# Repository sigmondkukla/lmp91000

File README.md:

# EFR32BG24 Potentiostat Firmware & Debugger

This repository contains the C++ firmware for the custom potentiostat platform (featuring an LMP91000 analog front end, EFR32BG24 MCU, and an LSM6DSV IMU) alongside a Python-based real-time wireless BLE debugging client.

---

## 1. Prerequisites and Requirements

### Hardware

* Custom Potentiostat PCB (EFR32BG24, LMP91000, LSM6DSV)
* Segger J-Link or Simplicity Link Debugger
* A stable external power source (e.g., 3.3V bench power or a well-charged battery with adequate bulk capacitance)

### Software

* Simplicity Commander (added to your system PATH)
* Python 3.8 or newer
* Bleak Python library (for BLE communications)

---

## 2. Initial Setup (Wired Flashing)

Before the board can accept wireless updates, you must flash the bootloader and the initial application image via a physical JTAG/SWD debug connection.

### Step 1: Flash the Gecko Bootloader

The Gecko Bootloader is responsible for managing internal storage and installing GBL files. You must flash the combined bootloader image containing both the first-stage and main bootloader configurations.

```bash
commander flash bootloader-storage-internal-single-combined.s37 --device EFR32BG24

```

### Step 2: Flash the Application Firmware

Flash the initial C++ application binary:

```bash
commander flash potentiostat_app.s37 --device EFR32BG24

```

---

## 3. Over-The-Air (OTA) Firmware Updates

The custom board supports wireless updates using the Silicon Labs Apploader. When the board reboots into OTA mode, it will advertise as `OTA_potentiostat`.

### OTA Update Steps
#### *Make sure to hold down the power button during the entire OTA upload process, and for about 15-20 seconds after it finishes*

1. Build the firmware project to generate your target `.gbl` file.
2. Put the device into OTA mode. The device will stop regular advertising and begin advertising as `OTA_potentiostat`.
3. Open the **EFR Connect** app on your smartphone or pc.
4. Scan and connect to **OTA_potentiostat**.
5. Select **OTA DFU**, choose **Partial OTA** (or select your `.gbl` file), and initiate the transfer.
6. Upon reaching 100%, the chip will reboot, verify the image, and boot into your new application.

---

## 4. Real-Time Wireless Log Stream

The firmware includes a high-speed wireless logger that routes standard debug prints over a custom BLE characteristic.

### Installation

Install the required asynchronous BLE library:

```bash
pip install bleak

```

### Python Logger Client: `ble_logger.py`

### Usage

1. Power on your potentiostat board.
2. Run the client script:
```bash
python ble_logger.py

```

3. The script will automatically scan, establish a secure BLE connection to your EFR32, subscribe to the notifications, and print custom `ble_printf` debug logs directly to your console.

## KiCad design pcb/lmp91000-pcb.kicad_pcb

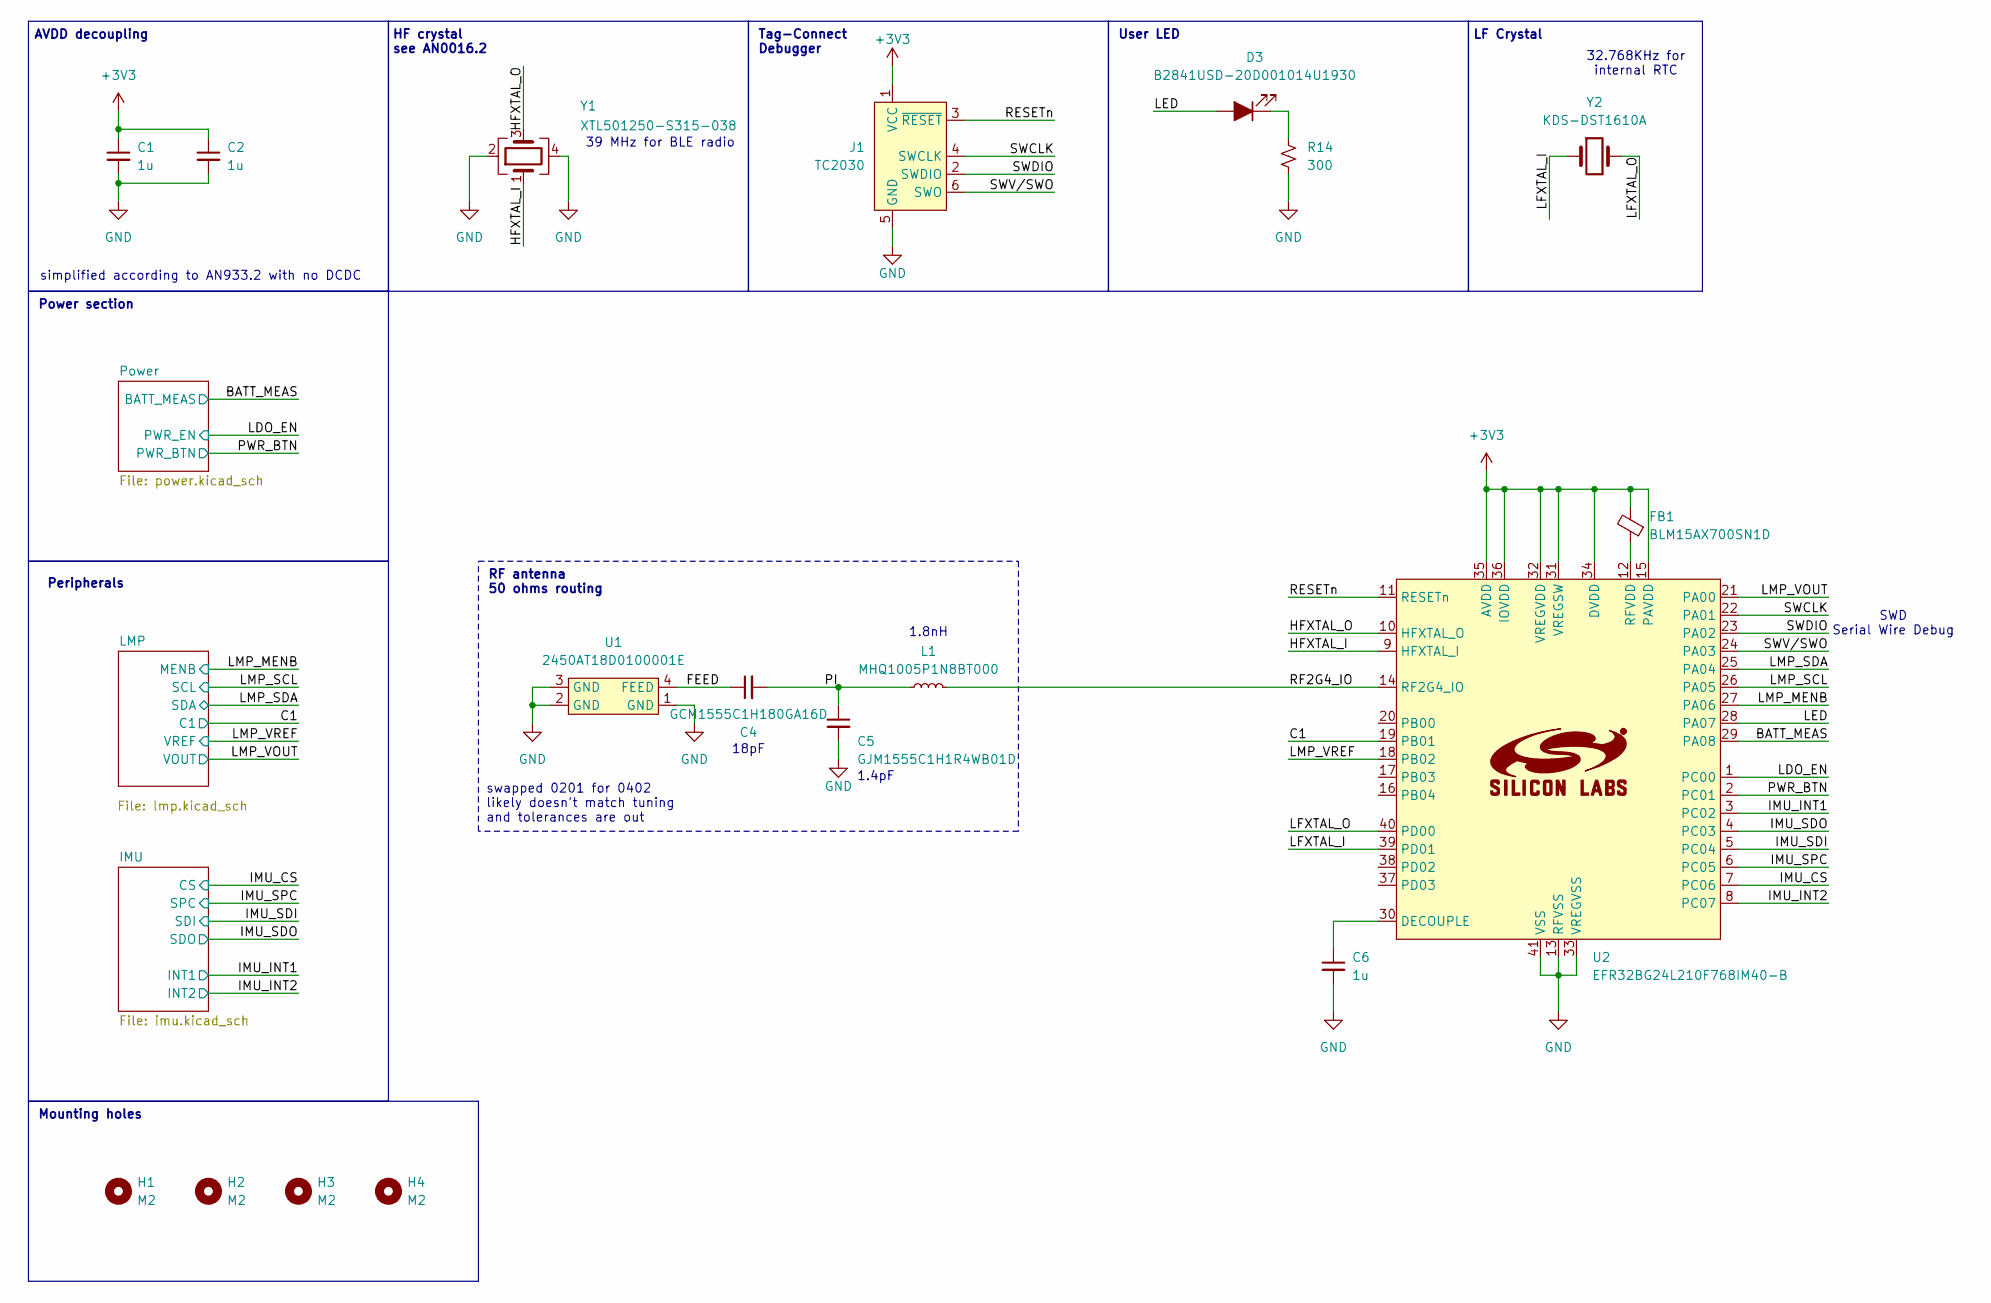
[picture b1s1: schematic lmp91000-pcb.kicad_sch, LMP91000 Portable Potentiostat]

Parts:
C1, C2, C6: 1u; C_0402_1005Metric
C4: GCM1555C1H180GA16D; C_0402_1005Metric
C5: GJM1555C1H1R4WB01D; C_0402_1005Metric
D3: B2841USD-20D001014U1930; LED_0402_1005Metric
FB1: BLM15AX700SN1D; L_0402_1005Metric
H1, H2, H3, H4: M2; MountingHole_2.2mm_M2
J1: TC2030; Tag-Connect_TC2030-IDC-NL_2x03_P1.27mm_Vertical
L1: MHQ1005P1N8BT000; L_0402_1005Metric
R14: 300; R_0402_1005Metric
U1: 2450AT18D0100001E; Johanson_2450AT18D0100001E
U2: EFR32BG24L210F768IM40-B; QFN-40-1EP_5x5mm_P0.4mm_EP3.8x3.8mm
Y1: XTL501250-S315-038; Crystal_SMD_2016-4Pin_2.0x1.6mm
Y2: KDS-DST1610A

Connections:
+3V3: C1.1, C2.1, FB1.2, J1.1 (VCC), U2.15 (PAVDD), U2.31 (VREGSW), U2.32 (VREGVDD), U2.34 (DVDD), U2.35 (AVDD), U2.36 (IOVDD); also elsewhere on the board
/BATT_MEAS: U2.29 (PA08); also elsewhere on the board
/C1: U2.19 (PB01); also elsewhere on the board
/FEED: C4.1, U1.4 (FEED)
/HFXTAL_I: U2.9 (HFXTAL_I), Y1.1
/HFXTAL_O: U2.10 (HFXTAL_O), Y1.3
/IMU_CS: U2.7 (PC06); also elsewhere on the board
/IMU_INT1: U2.3 (PC02); also elsewhere on the board
/IMU_INT2: U2.8 (PC07); also elsewhere on the board
/IMU_SDI: U2.5 (PC04); also elsewhere on the board
/IMU_SDO: U2.4 (PC03); also elsewhere on the board
/IMU_SPC: U2.6 (PC05); also elsewhere on the board
/LDO_EN: U2.1 (PC00); also elsewhere on the board
/LED: D3.2 (A), U2.28 (PA07)
/LFXTAL_I: U2.39 (PD01), Y2.1
/LFXTAL_O: U2.40 (PD00), Y2.2
/LMP_MENB: U2.27 (PA06); also elsewhere on the board
/LMP_SCL: U2.26 (PA05); also elsewhere on the board
/LMP_SDA: U2.25 (PA04); also elsewhere on the board
/LMP_VOUT: U2.21 (PA00); also elsewhere on the board
/LMP_VREF: U2.18 (PB02); also elsewhere on the board
/PI: C4.2, C5.1, L1.1
/PWR_BTN: U2.2 (PC01); also elsewhere on the board
/RESETn: J1.3 (~RESET), U2.11 (RESETn)
/RF2G4_IO: L1.2, U2.14 (RF2G4_IO)
/SWCLK: J1.4 (SWCLK), U2.22 (PA01)
/SWDIO: J1.2 (SWDIO), U2.23 (PA02)
/SWV/SWO: J1.6 (SWO), U2.24 (PA03)
GND: C1.2, C2.2, C5.2, C6.2, J1.5 (GND), R14.2, U1.1 (GND), U1.2 (GND), U1.3 (GND), U2.13 (RFVSS), U2.33 (VREGVSS), U2.41 (VSS), Y1.2, Y1.4; also elsewhere on the board
unnamed: D3.1 (K), R14.1
unnamed: C6.1, U2.30 (DECOUPLE)
unnamed: FB1.1, U2.12 (RFVDD)

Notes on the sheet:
1.4pF
User LED
Peripherals
1.8nH
32.768KHz for internal RTC
simplified according to AN933.2 with no DCDC
HF crystal see AN0016.2
SWD Serial Wire Debug
RF antenna 50 ohms routing
Tag-Connect Debugger
Mounting holes
39 MHz for BLE radio
LF Crystal
swapped 0201 for 0402 likely doesn't match tuning and tolerances are out
18pF
Power section
AVDD decoupling

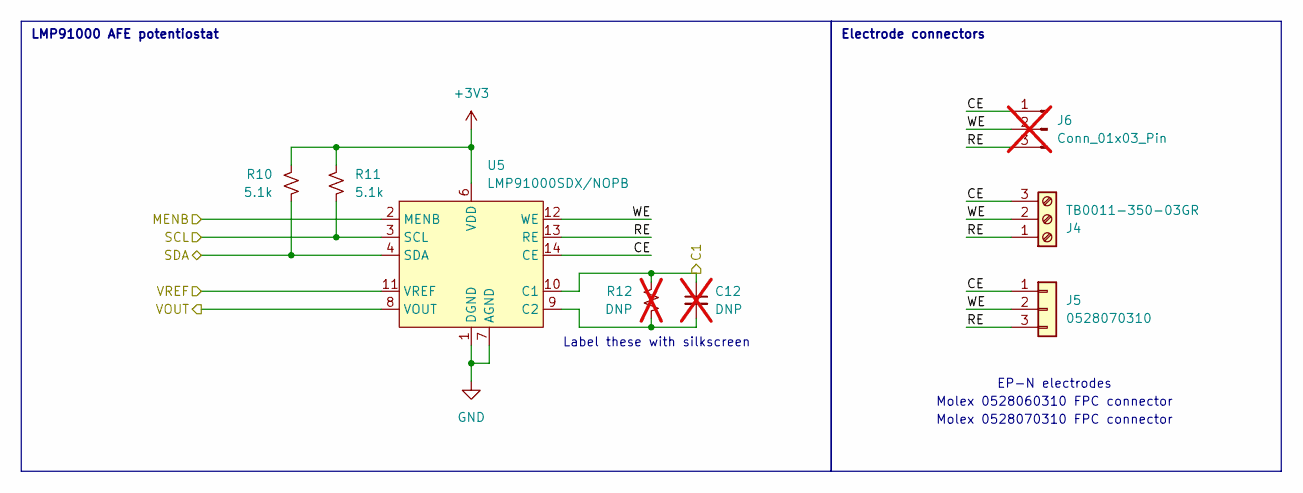
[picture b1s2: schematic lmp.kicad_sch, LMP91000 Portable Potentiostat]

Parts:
C12: DNP; C_0603_1608Metric_Pad1.08x0.95mm_HandSolder; not fitted
J4: TB0011-350-03GR; SAMESKY_TB0011-350-03GR
J5: 0528070310; 528070310
J6: Conn_01x03_Pin; PinHeader_1x03_P2.54mm_Vertical; not fitted
R10, R11: 5.1k; R_0402_1005Metric
R12: DNP; R_0603_1608Metric_Pad0.98x0.95mm_HandSolder; not fitted
U5: LMP91000SDX/NOPB; WSON-14-1EP_4.0x4.0mm_P0.5mm_EP2.6x2.6mm

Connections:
+3V3: R10.2, R11.2, U5.6 (VDD); also elsewhere on the board
/C1: C12.1, R12.1, U5.10 (C1); also elsewhere on the board
/LMP/CE: J4.3, J5.1, J6.1, U5.14 (CE)
/LMP/RE: J4.1, J5.3, J6.3, U5.13 (RE)
/LMP/WE: J4.2, J5.2, J6.2, U5.12 (WE)
/LMP_MENB: U5.2 (MENB); also elsewhere on the board
/LMP_SCL: R11.1, U5.3 (SCL); also elsewhere on the board
/LMP_SDA: R10.1, U5.4 (SDA); also elsewhere on the board
/LMP_VOUT: U5.8 (VOUT); also elsewhere on the board
/LMP_VREF: U5.11 (VREF); also elsewhere on the board
GND: U5.1 (DGND), U5.7 (AGND), U5.15 (DAP); also elsewhere on the board
unnamed: C12.2, R12.2, U5.9 (C2)

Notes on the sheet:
Label these with silkscreen
Molex 0528070310 FPC connector
EP-N electrodes
Molex 0528060310 FPC connector
LMP91000 AFE potentiostat
Electrode connectors

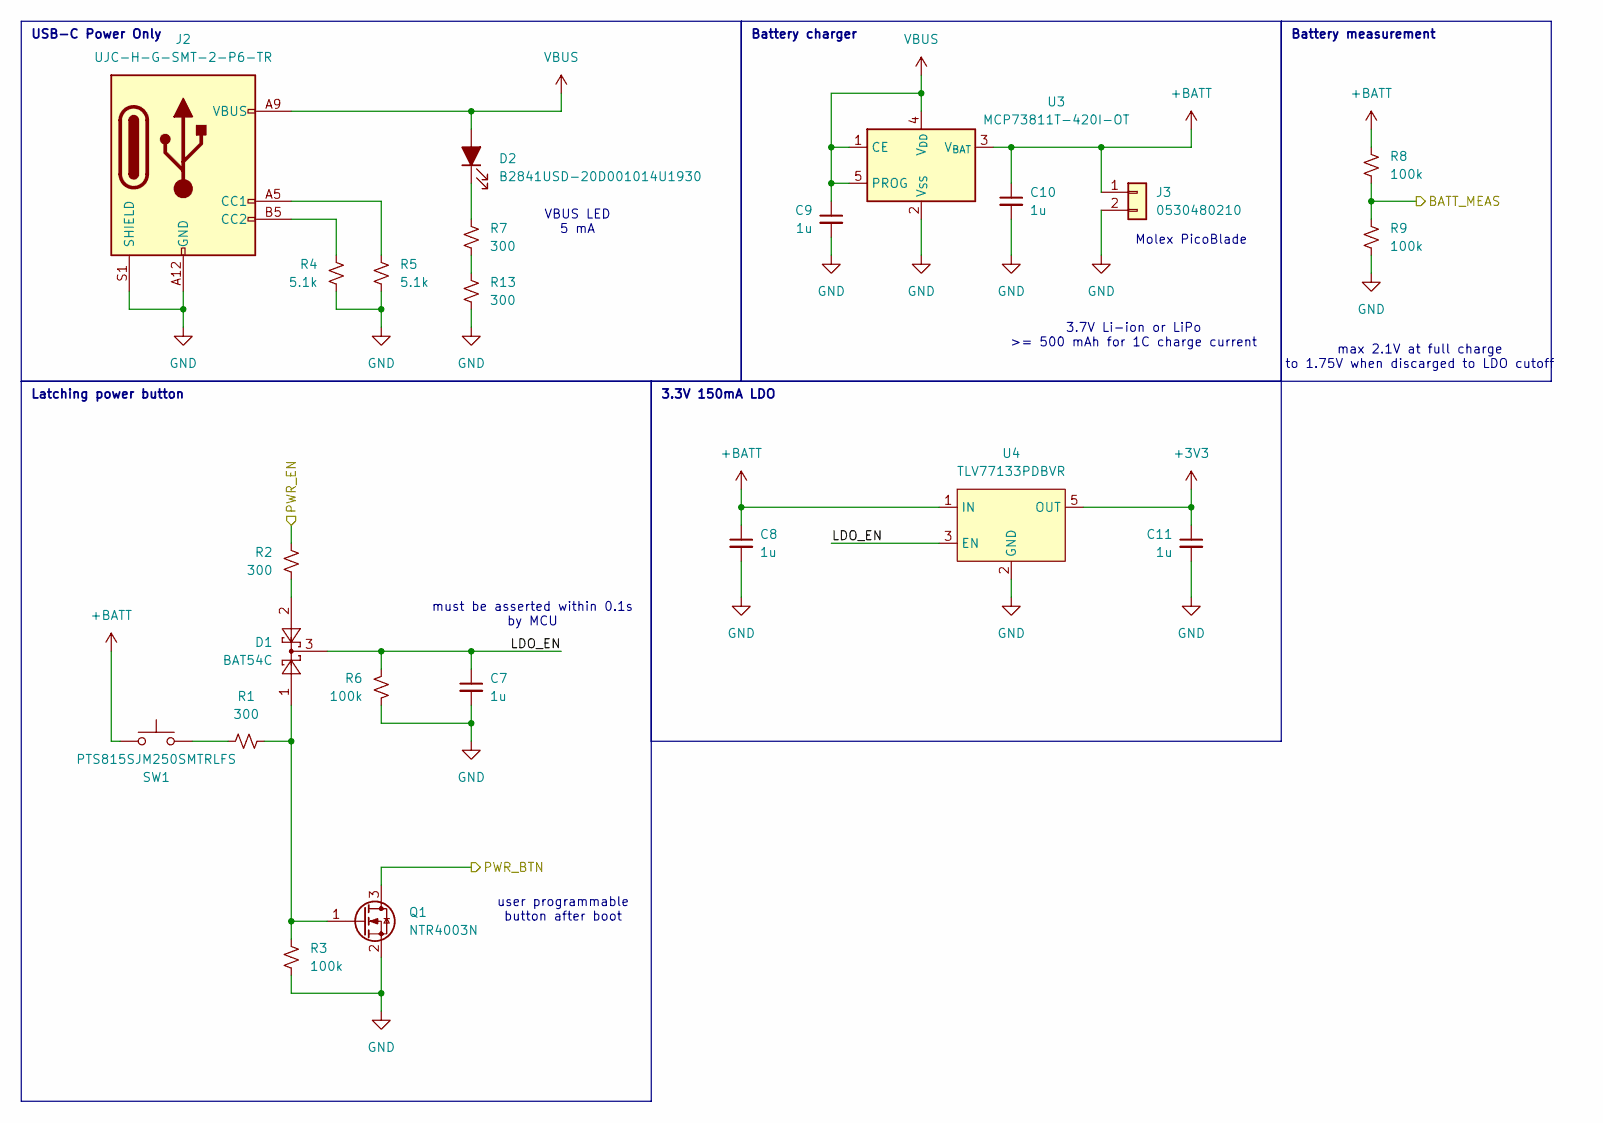
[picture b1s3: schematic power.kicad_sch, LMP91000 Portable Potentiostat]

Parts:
C7, C8, C9, C10, C11: 1u; C_0402_1005Metric
D1: BAT54C; SOT-23
D2: B2841USD-20D001014U1930; LED_0402_1005Metric
J2: UJC-H-G-SMT-2-P6-TR; SAMESKY_UJC-H-G-SMT-2-P6-TR
J3: 0530480210; Molex_PicoBlade_53048-0210_1x02_P1.25mm_Horizontal
Q1: NTR4003N; SOT-23
R1, R2, R7, R13: 300; R_0402_1005Metric
R3, R6, R8, R9: 100k; R_0402_1005Metric
R4, R5: 5.1k; R_0402_1005Metric
SW1: PTS815SJM250SMTRLFS; SW_Push_PTS815_SJM_250_SMTR_LFS
U3: MCP73811T-420I-OT; SOT-23-5
U4: TLV77133PDBVR; SOT-23-5

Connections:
+3V3: C11.1, U4.5 (OUT); also elsewhere on the board
+BATT: C8.1, C10.1, J3.1, R8.1, SW1.1, U3.3 (V_{BAT}), U4.1 (IN)
/BATT_MEAS: R8.2, R9.1; also elsewhere on the board
/LDO_EN: R2.1; also elsewhere on the board
/PWR_BTN: Q1.3 (D); also elsewhere on the board
/Power/LDO_EN: C7.1, D1.3, R6.1, U4.3 (EN)
GND: C7.2, C8.2, C9.2, C10.2, C11.2, J2.A12 (GND), J2.B12 (GND), J2.S1 (SHIELD), J3.2, Q1.2 (S), R3.2, R4.1, R5.1, R6.2, R9.2, R13.2, U3.2 (V_{SS}), U4.2 (GND), U4.4 (NC); also elsewhere on the board
unnamed: D1.2, R2.2
unnamed: D2.1 (K), R7.1
unnamed: J2.A5 (CC1), R5.2
unnamed: J2.B5 (CC2), R4.2
unnamed: D1.1, Q1.1 (G), R1.2, R3.1
unnamed: R1.1, SW1.2
unnamed: R7.2, R13.1
VBUS: C9.1, D2.2 (A), J2.A9 (VBUS), J2.B9 (VBUS), U3.1 (CE), U3.4 (V_{DD}), U3.5 (PROG)

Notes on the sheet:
USB-C Power Only
must be asserted within 0.1s by MCU
3.7V Li-ion or LiPo >= 500 mAh for 1C charge current
VBUS LED 5 mA
Molex PicoBlade
Battery charger
Battery measurement
Latching power button
3.3V 150mA LDO
user programmable button after boot
max 2.1V at full charge to 1.75V when discarged to LDO cutoff

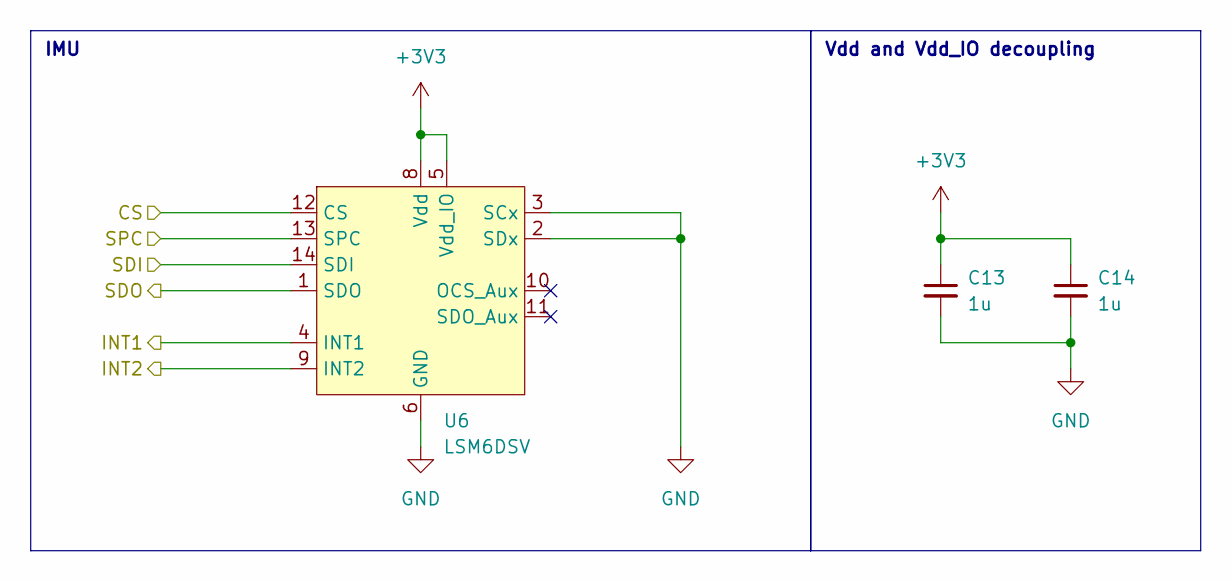
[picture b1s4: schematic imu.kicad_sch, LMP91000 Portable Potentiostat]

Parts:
C13, C14: 1u; C_0402_1005Metric
U6: LSM6DSV; LGA-14_3x2.5mm_P0.5mm_LayoutBorder3x4y

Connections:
+3V3: C13.1, C14.1, U6.5 (Vdd_IO), U6.8 (Vdd); also elsewhere on the board
/IMU_CS: U6.12 (CS); also elsewhere on the board
/IMU_INT1: U6.4 (INT1); also elsewhere on the board
/IMU_INT2: U6.9 (INT2); also elsewhere on the board
/IMU_SDI: U6.14 (SDI); also elsewhere on the board
/IMU_SDO: U6.1 (SDO); also elsewhere on the board
/IMU_SPC: U6.13 (SPC); also elsewhere on the board
GND: C13.2, C14.2, U6.2 (SDx), U6.3 (SCx), U6.6 (GND), U6.7 (GND); also elsewhere on the board

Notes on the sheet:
IMU
Vdd and Vdd_IO decoupling

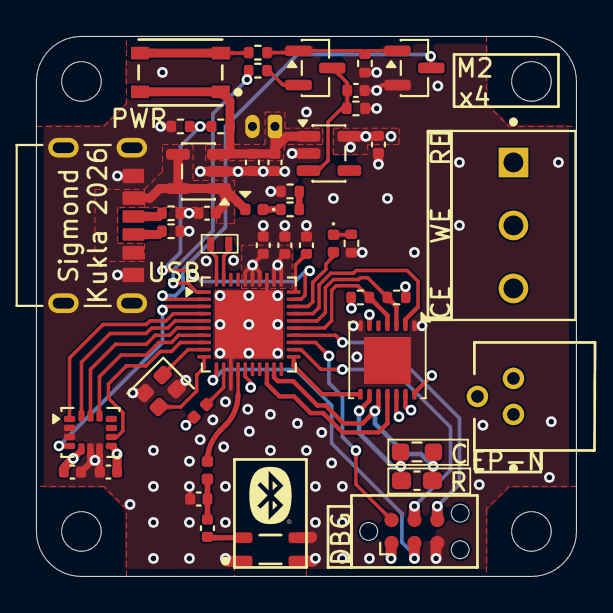
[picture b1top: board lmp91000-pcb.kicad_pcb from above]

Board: 4 copper layers, 30.0 x 30.0 mm, 51 parts (1 on the bottom side), 46 nets.

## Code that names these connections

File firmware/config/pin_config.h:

#ifndef PIN_CONFIG_H
#define PIN_CONFIG_H

// $[CMU]
// [CMU]$

// $[LFXO]
// [LFXO]$

// $[PRS.ASYNCH0]
// [PRS.ASYNCH0]$

// $[PRS.ASYNCH1]
// [PRS.ASYNCH1]$

// $[PRS.ASYNCH2]
// [PRS.ASYNCH2]$

// $[PRS.ASYNCH3]
// [PRS.ASYNCH3]$

// $[PRS.ASYNCH4]
// [PRS.ASYNCH4]$

// $[PRS.ASYNCH5]
// [PRS.ASYNCH5]$

// $[PRS.ASYNCH6]
// [PRS.ASYNCH6]$

// $[PRS.ASYNCH7]
// [PRS.ASYNCH7]$

// $[PRS.ASYNCH8]
// [PRS.ASYNCH8]$

// $[PRS.ASYNCH9]
// [PRS.ASYNCH9]$

// $[PRS.ASYNCH10]
// [PRS.ASYNCH10]$

// $[PRS.ASYNCH11]
// [PRS.ASYNCH11]$

// $[PRS.ASYNCH12]
// [PRS.ASYNCH12]$

// $[PRS.ASYNCH13]
// [PRS.ASYNCH13]$

// $[PRS.ASYNCH14]
// [PRS.ASYNCH14]$

// $[PRS.ASYNCH15]
// [PRS.ASYNCH15]$

// $[PRS.SYNCH0]
// [PRS.SYNCH0]$

// $[PRS.SYNCH1]
// [PRS.SYNCH1]$

// $[PRS.SYNCH2]
// [PRS.SYNCH2]$

// $[PRS.SYNCH3]
// [PRS.SYNCH3]$

// $[GPIO]
// GPIO SWCLK on PA01
#ifndef GPIO_SWCLK_PORT                         
#define GPIO_SWCLK_PORT                          SL_GPIO_PORT_A
#endif
#ifndef GPIO_SWCLK_PIN                          
#define GPIO_SWCLK_PIN                           1
#endif

// GPIO SWDIO on PA02
#ifndef GPIO_SWDIO_PORT                         
#define GPIO_SWDIO_PORT                          SL_GPIO_PORT_A
#endif
#ifndef GPIO_SWDIO_PIN                          
#define GPIO_SWDIO_PIN                           2
#endif

// GPIO SWV on PA03
#ifndef GPIO_SWV_PORT                           
#define GPIO_SWV_PORT                            SL_GPIO_PORT_A
#endif
#ifndef GPIO_SWV_PIN                            
#define GPIO_SWV_PIN                             3
#endif

// [GPIO]$

// $[TIMER0]
// [TIMER0]$

// $[TIMER1]
// [TIMER1]$

// $[TIMER2]
// [TIMER2]$

// $[TIMER3]
// [TIMER3]$

// $[TIMER4]
// [TIMER4]$

// $[USART0]
// [USART0]$

// $[I2C1]
// [I2C1]$

// $[EUSART1]
// [EUSART1]$

// $[KEYSCAN]
// [KEYSCAN]$

// $[LETIMER0]
// [LETIMER0]$

// $[IADC0]
// IADC0 POS on PA00
#ifndef IADC0_POS_PORT                          
#define IADC0_POS_PORT                           SL_GPIO_PORT_A
#endif
#ifndef IADC0_POS_PIN                           
#define IADC0_POS_PIN                            0
#endif

// [IADC0]$

// $[ACMP0]
// [ACMP0]$

// $[ACMP1]
// [ACMP1]$

// $[VDAC0]
// VDAC0 CH0_MAIN_OUT on PB00
#ifndef VDAC0_CH0_MAIN_OUT_PORT                 
#define VDAC0_CH0_MAIN_OUT_PORT                  SL_GPIO_PORT_B
#endif
#ifndef VDAC0_CH0_MAIN_OUT_PIN                  
#define VDAC0_CH0_MAIN_OUT_PIN                   0
#endif

// [VDAC0]$

// $[VDAC1]
// [VDAC1]$

// $[PCNT0]
// [PCNT0]$

// $[HFXO0]
// [HFXO0]$

// $[I2C0]
// I2C0 SCL on PA05
#ifndef I2C0_SCL_PORT                           
#define I2C0_SCL_PORT                            SL_GPIO_PORT_A
#endif
#ifndef I2C0_SCL_PIN                            
#define I2C0_SCL_PIN                             5
#endif

// I2C0 SDA on PA04
#ifndef I2C0_SDA_PORT                           
#define I2C0_SDA_PORT                            SL_GPIO_PORT_A
#endif
#ifndef I2C0_SDA_PIN                            
#define I2C0_SDA_PIN                             4
#endif

// [I2C0]$

// $[EUSART0]
// [EUSART0]$

// $[PTI]
// [PTI]$

// $[MODEM]
// [MODEM]$

// $[CUSTOM_PIN_NAME]
#ifndef LMP_VOUT_PORT                           
#define LMP_VOUT_PORT                            SL_GPIO_PORT_A
#endif
#ifndef LMP_VOUT_PIN                            
#define LMP_VOUT_PIN                             0
#endif

#ifndef LMP_SDA_PORT                            
#define LMP_SDA_PORT                             SL_GPIO_PORT_A
#endif
#ifndef LMP_SDA_PIN                             
#define LMP_SDA_PIN                              4
#endif

#ifndef LMP_SCL_PORT                            
#define LMP_SCL_PORT                             SL_GPIO_PORT_A
#endif
#ifndef LMP_SCL_PIN                             
#define LMP_SCL_PIN                              5
#endif

#ifndef LED_PORT                                
#define LED_PORT                                 SL_GPIO_PORT_A
#endif
#ifndef LED_PIN                                 
#define LED_PIN                                  8
#endif

#ifndef LMP_VREF_PORT                           
#define LMP_VREF_PORT                            SL_GPIO_PORT_B
#endif
#ifndef LMP_VREF_PIN                            
#define LMP_VREF_PIN                             0
#endif

#ifndef LDO_EN_PORT                             
#define LDO_EN_PORT                              SL_GPIO_PORT_C
#endif
#ifndef LDO_EN_PIN                              
#define LDO_EN_PIN                               0
#endif

#ifndef PWR_BTN_PORT                            
#define PWR_BTN_PORT                             SL_GPIO_PORT_C
#endif
#ifndef PWR_BTN_PIN                             
#define PWR_BTN_PIN                              1
#endif

#ifndef IMU_SDO_PORT                            
#define IMU_SDO_PORT                             SL_GPIO_PORT_C
#endif
#ifndef IMU_SDO_PIN                             
#define IMU_SDO_PIN                              3
#endif

#ifndef IMU_SDI_PORT                            
#define IMU_SDI_PORT                             SL_GPIO_PORT_C
#endif
#ifndef IMU_SDI_PIN                             
#define IMU_SDI_PIN                              4
#endif

#ifndef IMU_SPC_PORT                            
#define IMU_SPC_PORT                             SL_GPIO_PORT_C
#endif
#ifndef IMU_SPC_PIN                             
#define IMU_SPC_PIN                              5
#endif

#ifndef IMU_CS_PORT                             
#define IMU_CS_PORT                              SL_GPIO_PORT_C
#endif
#ifndef IMU_CS_PIN                              
#define IMU_CS_PIN                               6
#endif

#ifndef IMU_INT2_PORT                           
#define IMU_INT2_PORT                            SL_GPIO_PORT_C
#endif
#ifndef IMU_INT2_PIN                            
#define IMU_INT2_PIN                             7
#endif

#ifndef BATT_MEAS_PORT                          
#define BATT_MEAS_PORT                           SL_GPIO_PORT_D
#endif
#ifndef BATT_MEAS_PIN                           
#define BATT_MEAS_PIN                            0
#endif

// [CUSTOM_PIN_NAME]$


#endif // PIN_CONFIG_H

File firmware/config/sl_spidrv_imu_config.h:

/***************************************************************************//**
 * @file
 * @brief SPIDRV Config
 *******************************************************************************
 * # License
 * <b>Copyright 2019 Silicon Laboratories Inc. www.silabs.com</b>
 *******************************************************************************
 *
 * SPDX-License-Identifier: Zlib
 *
 * The licensor of this software is Silicon Laboratories Inc.
 *
 * This software is provided 'as-is', without any express or implied
 * warranty. In no event will the authors be held liable for any damages
 * arising from the use of this software.
 *
 * Permission is granted to anyone to use this software for any purpose,
 * including commercial applications, and to alter it and redistribute it
 * freely, subject to the following restrictions:
 *
 * 1. The origin of this software must not be misrepresented; you must not
 *    claim that you wrote the original software. If you use this software
 *    in a product, an acknowledgment in the product documentation would be
 *    appreciated but is not required.
 * 2. Altered source versions must be plainly marked as such, and must not be
 *    misrepresented as being the original software.
 * 3. This notice may not be removed or altered from any source distribution.
 *
 ******************************************************************************/

#ifndef SL_SPIDRV_IMU_CONFIG_H
#define SL_SPIDRV_IMU_CONFIG_H

#include "spidrv.h"

// <<< Use Configuration Wizard in Context Menu >>>
// <h> SPIDRV settings

// <o SL_SPIDRV_IMU_BITRATE> SPI bitrate
// <i> Default: 1000000
#define SL_SPIDRV_IMU_BITRATE           1000000

// <o SL_SPIDRV_IMU_FRAME_LENGTH> SPI frame length <4-16>
// <i> Default: 8
#define SL_SPIDRV_IMU_FRAME_LENGTH      8

// <o SL_SPIDRV_IMU_TYPE> SPI mode
// <spidrvMaster=> Master
// <spidrvSlave=> Slave
#define SL_SPIDRV_IMU_TYPE              spidrvMaster

// <o SL_SPIDRV_IMU_BIT_ORDER> Bit order on the SPI bus
// <spidrvBitOrderLsbFirst=> LSB transmitted first
// <spidrvBitOrderMsbFirst=> MSB transmitted first
#define SL_SPIDRV_IMU_BIT_ORDER         spidrvBitOrderMsbFirst

// <o SL_SPIDRV_IMU_CLOCK_MODE> SPI clock mode
// <spidrvClockMode0=> SPI mode 0: CLKPOL=0, CLKPHA=0
// <spidrvClockMode1=> SPI mode 1: CLKPOL=0, CLKPHA=1
// <spidrvClockMode2=> SPI mode 2: CLKPOL=1, CLKPHA=0
// <spidrvClockMode3=> SPI mode 3: CLKPOL=1, CLKPHA=1
#define SL_SPIDRV_IMU_CLOCK_MODE        spidrvClockMode0

// <o SL_SPIDRV_IMU_CS_CONTROL> SPI master chip select (CS) control scheme.
// <spidrvCsControlAuto=> CS controlled by the SPI driver
// <spidrvCsControlApplication=> CS controlled by the application
#define SL_SPIDRV_IMU_CS_CONTROL        spidrvCsControlAuto

// <o SL_SPIDRV_IMU_SLAVE_START_MODE> SPI slave transfer start scheme
// <spidrvSlaveStartImmediate=> Transfer starts immediately
// <spidrvSlaveStartDelayed=> Transfer starts when the bus is idle (CS deasserted)
// <i> Only applies if instance type is spidrvSlave
#define SL_SPIDRV_IMU_SLAVE_START_MODE  spidrvSlaveStartImmediate
// </h>
// <<< end of configuration section >>>

// <<< sl:start pin_tool >>>
// <usart signal=TX,RX,CLK,(CS)> SL_SPIDRV_IMU
// $[USART_SL_SPIDRV_IMU]
#ifndef SL_SPIDRV_IMU_PERIPHERAL                
#define SL_SPIDRV_IMU_PERIPHERAL                 USART0
#endif
#ifndef SL_SPIDRV_IMU_PERIPHERAL_NO             
#define SL_SPIDRV_IMU_PERIPHERAL_NO              0
#endif

// USART0 TX on PC04
#ifndef SL_SPIDRV_IMU_TX_PORT                   
#define SL_SPIDRV_IMU_TX_PORT                    SL_GPIO_PORT_C
#endif
#ifndef SL_SPIDRV_IMU_TX_PIN                    
#define SL_SPIDRV_IMU_TX_PIN                     4
#endif

// USART0 RX on PC03
#ifndef SL_SPIDRV_IMU_RX_PORT                   
#define SL_SPIDRV_IMU_RX_PORT                    SL_GPIO_PORT_C
#endif
#ifndef SL_SPIDRV_IMU_RX_PIN                    
#define SL_SPIDRV_IMU_RX_PIN                     3
#endif

// USART0 CLK on PC05
#ifndef SL_SPIDRV_IMU_CLK_PORT                  
#define SL_SPIDRV_IMU_CLK_PORT                   SL_GPIO_PORT_C
#endif
#ifndef SL_SPIDRV_IMU_CLK_PIN                   
#define SL_SPIDRV_IMU_CLK_PIN                    5
#endif

// USART0 CS on PC06
#ifndef SL_SPIDRV_IMU_CS_PORT                   
#define SL_SPIDRV_IMU_CS_PORT                    SL_GPIO_PORT_C
#endif
#ifndef SL_SPIDRV_IMU_CS_PIN                    
#define SL_SPIDRV_IMU_CS_PIN                     6
#endif
// [USART_SL_SPIDRV_IMU]$
// <<< sl:end pin_tool >>>

#endif // SL_SPIDRV_IMU_CONFIG_H



// [USART_SL_SPIDRV_IMU]$
// <<< sl:end pin_tool >>>

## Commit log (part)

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2026-01-21 Initial project commit
2026-01-21 Add datasheets
2026-01-21 Update kicad-library-sigmondkukla
2026-01-21 Remove reset button
2026-01-21 Simplify to minimum buck converter components
2026-01-26 Assign footprints, cleanup schematics, start layout
2026-01-27 Finish PCB
2026-01-28 Create fabrication files
2026-01-28 Move antenna and tag connect
2026-01-28 Shrink PCB page and center on page
2026-01-28 Adjust RF trace grounding
2026-01-28 Cleaned up routing
2026-01-28 Run DRC
2026-01-28 Remove old production files
2026-01-28 Update back silkscreen with labels
2026-03-23 Create Simplicity Studio 6 firmware project
2026-04-06 Update pin config
2026-04-06 Use I2C ports and pins for initialization
2026-04-06 Update ADC
2026-04-06 Switch from SPI DAC to on-chip VDAC
2026-04-08 Begin cpp upgrade
2026-04-08 Fix LMP_VOUT input
2026-04-08 Change angle brackets to quotes for experiment header includes
2026-04-08 Add app log
2026-04-08 Get successful C++ build
2026-04-08 Working CMakeLists.txt
2026-04-16 added initial lsm6dsv class structure and implementation
2026-04-17 syntax error fx
2026-04-17 function signitures and SPI testing
2026-04-20 small fixes
2026-04-21 working USART0 implementation
2026-04-22 Simple Scan Queue read implemented
2026-04-22 Abstract battery voltage function into separate implementation
2026-04-23 Fixed battery read function and added float linker flag
2026-04-23 implementation for all getters and expample print code
2026-04-27 Build project
2026-04-28 small polish
2026-04-28 fixing up app.cpp
2026-04-28 bringing app.cpp back to original state
2026-05-07 Fix i2c for new board design
2026-05-07 Readd expirement functionality
2026-05-27 ignore
2026-05-27 Second Commit
2026-05-27 Led Blinking
2026-05-27 Testing
2026-05-27 Test
2026-05-27 zach and matt branch merge
2026-06-01 things are working
2026-06-01 status configuration working with apply button
2026-06-01 Led Blinking 500
2026-06-01 APP FINALLY WORKS!!!!
2026-06-03 small DAC output changes
2026-06-03 removed broken files
2026-06-04 removed all printf debug messages
2026-06-05 print out csv in terminal
2026-06-05 assert power button pin
2026-06-05 power indicator led
2026-06-08 Fix Button Pressed State
2026-06-08 Adjusted comments and organized app.cpp
2026-06-08 Board blinks 3 times then turns off demo
2026-06-08 go back 3 commits haha
2026-06-08 Data finally consistent
2026-06-08 Power Button Works! The board turns on and off.
2026-06-09 Battery Readout is Enabled
2026-06-11 preventing i2c flooding by only changing bias settings when necessary, added debug prints for BLE notifications and experiment ticks. this allows bluetooth to send live notifications more reliably.
2026-06-11 set outputs to 0 after experiment ends
2026-06-12 deep sleep lmp after experiment
2026-06-15 Sleeps in EM4 for 5 seconds, then wakes up
2026-06-15 reset previous values after experiment end, experiments now work back to back!
2026-06-15 improved output_voltage function to prevent reboots
2026-06-15 put lmp to sleep after experiments (uncommented)
2026-06-15 Organized code and separated burtc.c and burtc.h into separate files.
2026-06-17 Troubleshooting Battery Readout
2026-06-17 improved bias setting optimizaition
2026-06-17 Update battery reading line
2026-06-17 Organized Files
2026-06-17 Goes into EM4 for 10 seconds then wakes up. Completed Code
2026-06-18 added new output voltage function for CV, DPV, SWV
2026-06-18 make vref change based on current DAC output, (should fix shifting error)
2026-06-25 Add extra functions to burtc.c
2026-06-25 Polished: burtc.c is split into 3 functions
2026-06-26 SLCP Update
2026-06-26 Clean code of burtc.c in 3 functions
2026-06-26 Uncommented some commands
2026-06-26 Resets every two seconds and counter counts up probably
2026-06-26 Print out works
2026-06-26 Counts up properly (still has reset issue)
2026-06-26 Show reset reason
2026-06-26 Better Reset Causes
2026-06-26 Doesn't work on battery, but works with terminal
2026-06-29 Works on battery
2026-06-29 Yay! Timer starts at end of process.
2026-06-29 Cleared up some comments
2026-06-29 RTC works other than extra ticks with EM4 mode
2026-06-30 Timer is mostly accurate!
2026-06-30 RTC Works but can't be set
2026-06-30 RTC Works but need to add prescaler
2026-06-30 RTC and Timekeeping works with ULFRCO but is unaccurate
